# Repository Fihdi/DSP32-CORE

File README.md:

# DSP32-Core

DSP32-Core is a small (4cm x 2cm) audio development board based on the ESP32-S3. This board can be used as the core for digital music and audio applications involving synthesizers, samplers, digital effects, sequencers, etc. The SPI interface allows to connect an SD-card to the board and save and replay music and project settings.

# Features
+ Stereo audio in- and output
+ 3.3V and 5V voltage regulator
+ USB and SPI Interface
+ up to 15 GPIO pins
+ PCM1808 ADC
+ PCM5102 DAC.
# Pinout

PCB fabrication sponsored by [PCBWay](https://pcbway.com). Their excellent PCB assembly service allows the DSP32-CORE to be produced in with every component perfectly soldered. Simply upload the production files like gerbers, position and BOM files and receive your fully assembled audio development board. High PCB quality and good customer service throughout the process makes PCBWay a reliable partner.

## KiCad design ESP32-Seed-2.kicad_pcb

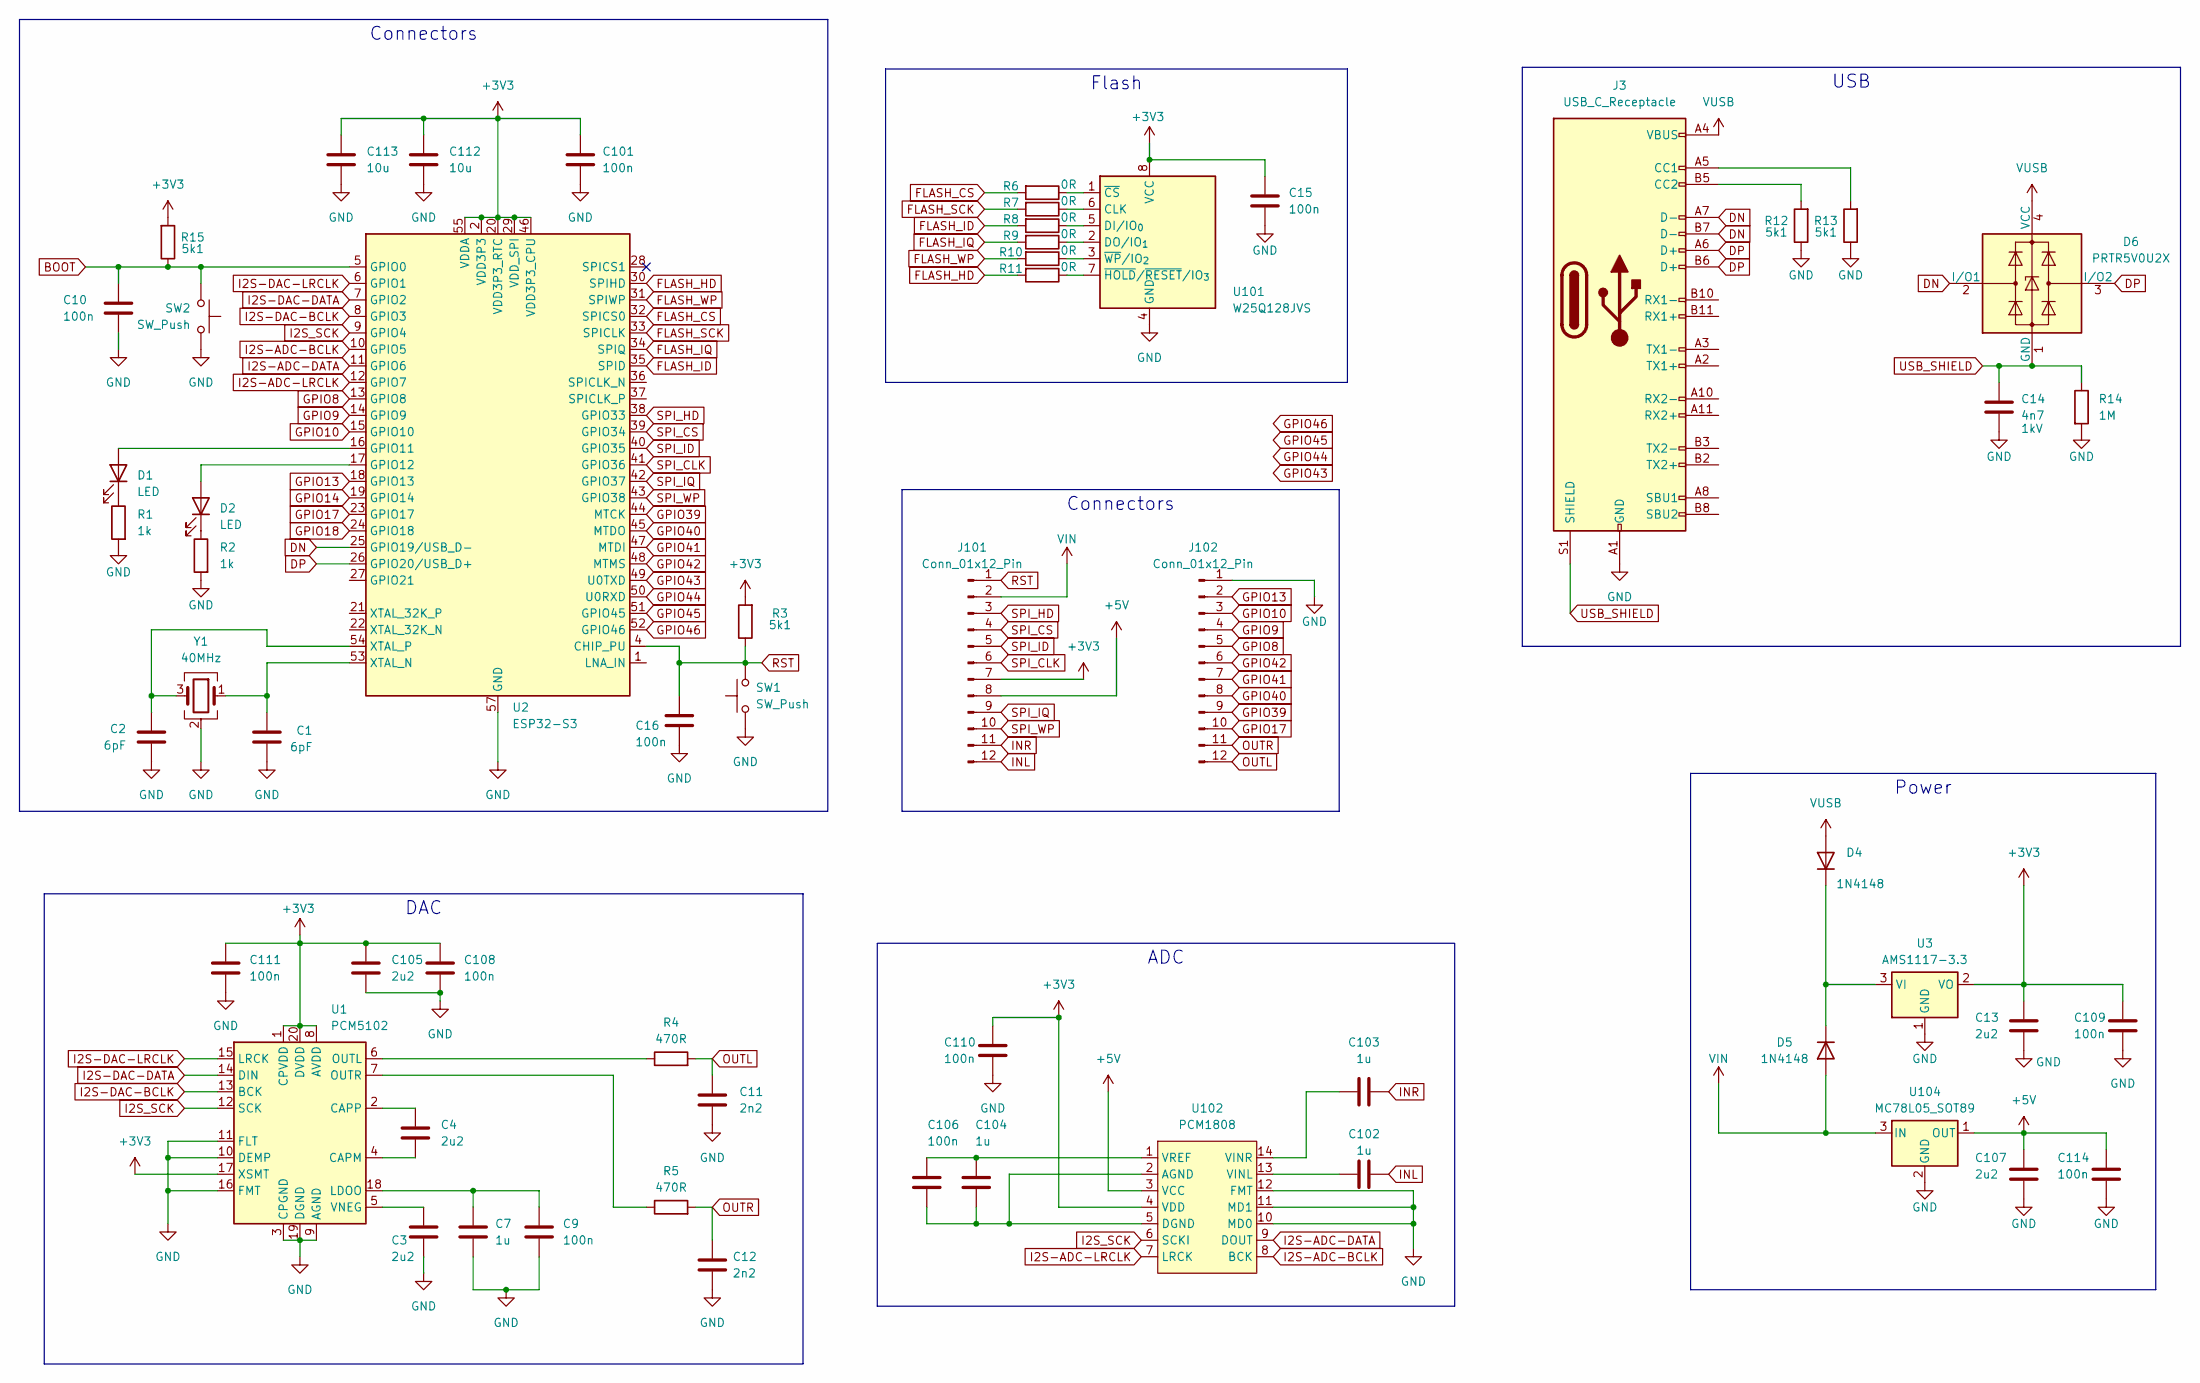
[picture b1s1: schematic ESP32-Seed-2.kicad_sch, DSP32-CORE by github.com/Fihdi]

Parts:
C1, C2: 6pF; C_0603_1608Metric
C3, C4, C13, C105, C107: 2u2; C_0603_1608Metric
C7, C102, C103, C104: 1u; C_0603_1608Metric
C9, C10, C15, C16, C101, C106, C108, C109, C110, C111, C114: 100n; C_0603_1608Metric
C11, C12: 2n2; C_0603_1608Metric
C14: 4n7; C_0603_1608Metric
C112, C113: 10u; C_0603_1608Metric
D1, D2: LED; LED_0603_1608Metric
D4, D5: 1N4148; D_SOD-323_HandSoldering
D6: PRTR5V0U2X; SOT-143
J3: USB_C_Receptacle; USB_C_Receptacle_GCT_USB4105-xx-A_16P_TopMnt_Horizontal
J101, J102: Conn_01x12_Pin; PinHeader_1x12_P2.54mm_Vertical
R1, R2: 1k; R_0603_1608Metric
R3, R12, R13, R15: 5k1; R_0603_1608Metric
R4, R5: 470R; R_0603_1608Metric
R6, R7, R8, R9, R10, R11: 0R; R_0603_1608Metric
R14: 1M; R_0603_1608Metric
SW1, SW2: SW_Push; SW_SPST_PTS810
U1: PCM5102; TSSOP-20_4.4x6.5mm_P0.65mm
U2: ESP32-S3; QFN-56-1EP_7x7mm_P0.4mm_EP4x4mm
U3: AMS1117-3.3; SOT-89-3
U101: W25Q128JVS; SOIC-8_5.3x5.3mm_P1.27mm
U102: PCM1808; TSSOP-14_4.4x5mm_P0.65mm
U104: MC78L05_SOT89; SOT-89-3
Y1: 40MHz; Crystal_SMD_3225-4Pin_3.2x2.5mm

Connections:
+3V3: C13.1, C15.1, C101.1, C105.1, C108.1, C109.1, C110.1, C111.1, C112.1, C113.1, J101.7, R3.2, R15.2, U1.1 (CPVDD), U1.8 (AVDD), U1.17 (XSMT), U1.20 (DVDD), U2.2 (VDD3P3), U2.3 (VDD3P3), U2.20 (VDD3P3_RTC), U2.29 (VDD_SPI), U2.46 (VDD3P3_CPU), U2.55 (VDDA), U2.56 (VDDA), U3.2 (VO), U101.8 (VCC), U102.4 (VDD)
+5V: C107.1, C114.1, J101.8, U102.3 (VCC), U104.1 (OUT)
BOOT: C10.1, R15.1, SW2.2, U2.5 (GPIO0)
DN: D6.2 (I/O1), J3.A7 (D-), J3.B7 (D-), U2.25 (GPIO19/USB_D-)
DP: D6.3 (I/O2), J3.A6 (D+), J3.B6 (D+), U2.26 (GPIO20/USB_D+)
FLASH_CS: R6.2, U2.32 (SPICS0)
FLASH_HD: R11.2, U2.30 (SPIHD)
FLASH_ID: R8.2, U2.35 (SPID)
FLASH_IQ: R9.2, U2.34 (SPIQ)
FLASH_SCK: R7.2, U2.33 (SPICLK)
FLASH_WP: R10.2, U2.31 (SPIWP)
GND: C1.2, C2.2, C3.2, C7.2, C9.2, C10.2, C11.2, C12.2, C13.2, C14.2, C15.2, C16.2, C101.2, C105.2, C107.2, C108.2, C109.2, C110.2, C111.2, C112.2, C113.2, C114.2, J3.A1 (GND), J3.A12 (GND), J3.B1 (GND), J3.B12 (GND), J102.1, R1.2, R2.2, R12.1, R13.1, R14.2, SW1.1, SW2.1, U1.3 (CPGND), U1.9 (AGND), U1.10 (DEMP), U1.11 (FLT), U1.16 (FMT), U1.19 (DGND), U2.57 (GND), U3.1 (GND), U101.4 (GND), U102.10 (MD0), U102.11 (MD1), U102.12 (FMT), U104.2 (GND), Y1.2 (G), Y1.4 (G)
GPIO8: J102.5, U2.13 (GPIO8)
GPIO9: J102.4, U2.14 (GPIO9)
GPIO10: J102.3, U2.15 (GPIO10)
GPIO13: J102.2, U2.18 (GPIO13)
GPIO14: U2.19 (GPIO14)
GPIO17: J102.10, U2.23 (GPIO17)
GPIO18: U2.24 (GPIO18)
GPIO39: J102.9, U2.44 (MTCK)
GPIO40: J102.8, U2.45 (MTDO)
GPIO41: J102.7, U2.47 (MTDI)
GPIO42: J102.6, U2.48 (MTMS)
GPIO43: U2.49 (U0TXD)
GPIO44: U2.50 (U0RXD)
GPIO45: U2.51 (GPIO45)
GPIO46: U2.52 (GPIO46)
I2S-ADC-BCLK: U2.10 (GPIO5), U102.8 (BCK)
I2S-ADC-DATA: U2.11 (GPIO6), U102.9 (DOUT)
I2S-ADC-LRCLK: U2.12 (GPIO7), U102.7 (LRCK)
I2S-DAC-BCLK: U1.13 (BCK), U2.8 (GPIO3)
I2S-DAC-DATA: U1.14 (DIN), U2.7 (GPIO2)
I2S-DAC-LRCLK: U1.15 (LRCK), U2.6 (GPIO1)
I2S_SCK: U1.12 (SCK), U2.9 (GPIO4), U102.6 (SCKI)
INL: C102.2, J101.12
INR: C103.2, J101.11
unnamed: D1.2 (A), U2.16 (GPIO11)
unnamed: D1.1 (K), R1.1
unnamed: D2.2 (A), U2.17 (GPIO12)
unnamed: D2.1 (K), R2.1
unnamed: D4.1 (K), D5.1 (K), U3.3 (VI)
unnamed: J3.A5 (CC1), R13.2
unnamed: J3.B5 (CC2), R12.2
unnamed: C4.2, U1.4 (CAPM)
unnamed: C4.1, U1.2 (CAPP)
unnamed: C7.1, C9.1, U1.18 (LDOO)
unnamed: R4.1, U1.6 (OUTL)
unnamed: R5.1, U1.7 (OUTR)
unnamed: C3.1, U1.5 (VNEG)
unnamed: C1.1, U2.53 (XTAL_N), Y1.1
unnamed: C2.1, U2.54 (XTAL_P), Y1.3
unnamed: R7.1, U101.6 (CLK)
unnamed: R8.1, U101.5 (DI/IO_{0})
unnamed: R9.1, U101.2 (DO/IO_{1})
unnamed: R6.1, U101.1 (~CS)
unnamed: R11.1, U101.7 (~HOLD/~RESET/IO_{3})
unnamed: R10.1, U101.3 (~WP/IO_{2})
unnamed: C104.2, C106.2, U102.2 (AGND), U102.5 (DGND)
unnamed: C102.1, U102.13 (VINL)
unnamed: C103.1, U102.14 (VINR)
unnamed: C104.1, C106.1, U102.1 (VREF)
OUTL: C11.1, J102.12, R4.2
OUTR: C12.1, J102.11, R5.2
RST: C16.1, J101.1, R3.1, SW1.2, U2.4 (CHIP_PU)
SPI_CLK: J101.6, U2.41 (GPIO36)
SPI_CS: J101.4, U2.39 (GPIO34)
SPI_HD: J101.3, U2.38 (GPIO33)
SPI_ID: J101.5, U2.40 (GPIO35)
SPI_IQ: J101.9, U2.42 (GPIO37)
SPI_WP: J101.10, U2.43 (GPIO38)
USB_SHIELD: C14.1, D6.1 (GND), J3.S1 (SHIELD), R14.1
VIN: D5.2 (A), J101.2, U104.3 (IN)
VUSB: D4.2 (A), D6.4 (VCC), J3.A4 (VBUS), J3.A9 (VBUS), J3.B4 (VBUS), J3.B9 (VBUS)

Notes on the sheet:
DAC
Connectors
Power
ADC
Flash
USB

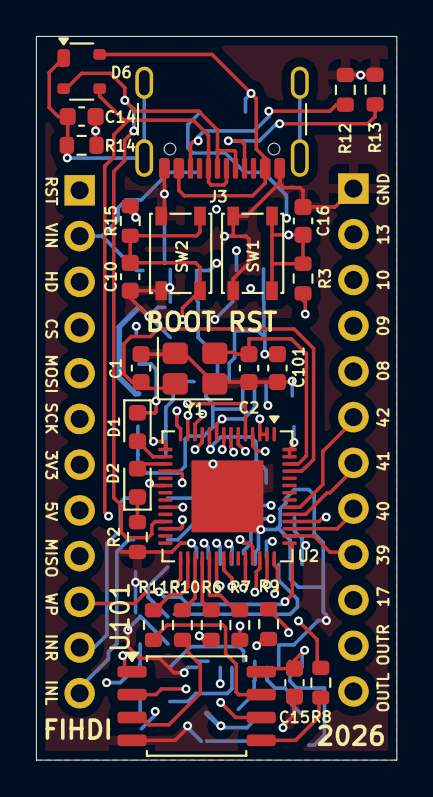
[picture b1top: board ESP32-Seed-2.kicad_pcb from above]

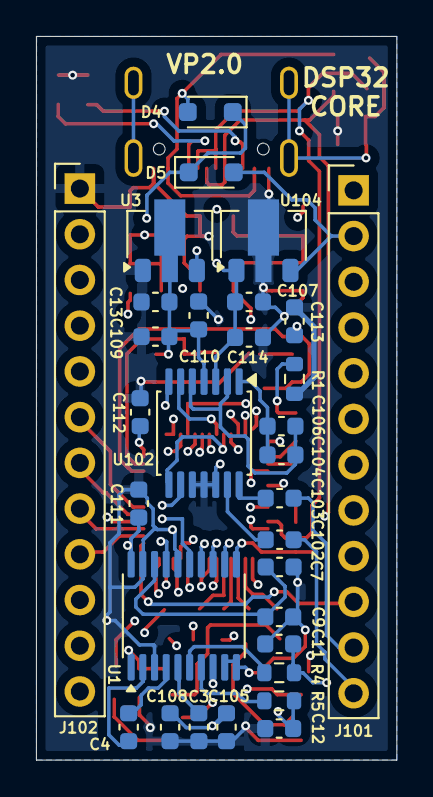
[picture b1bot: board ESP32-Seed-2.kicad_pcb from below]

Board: 4 copper layers, 20.0 x 40.2 mm, 59 parts (31 on the bottom side), 67 nets.

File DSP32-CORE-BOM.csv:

"Reference","Qty","Value","DNP","Exclude from BOM","Exclude from Board","Footprint","Datasheet"
"C1,C2","2","6pF","","","","Capacitor_SMD:C_0603_1608Metric","~"
"C3,C4,C13,C105,C107","5","2u2","","","","Capacitor_SMD:C_0603_1608Metric","~"
"C7,C102,C103,C104","4","1u","","","","Capacitor_SMD:C_0603_1608Metric","~"
"C9,C10,C15,C16,C101,C106,C108,C109,C110,C111,C114","11","100n","","","","Capacitor_SMD:C_0603_1608Metric","~"
"C11,C12","2","2n2","","","","Capacitor_SMD:C_0603_1608Metric","~"
"C14","1","4n7","","","","Capacitor_SMD:C_0603_1608Metric","~"
"C112,C113","2","10u","","","","Capacitor_SMD:C_0603_1608Metric","~"
"D1,D2","2","LED","","","","LED_SMD:LED_0603_1608Metric","~"
"D4,D5","2","1N4148","","","","Diode_SMD:D_SOD-323_HandSoldering","~"
"D6","1","PRTR5V0U2X","","","","Package_TO_SOT_SMD:SOT-143","https://assets.nexperia.com/documents/data-sheet/PRTR5V0U2X.pdf"
"J3","1","USB_C_Receptacle","","","","Connector_USB:USB_C_Receptacle_GCT_USB4105-xx-A_16P_TopMnt_Horizontal","https://www.usb.org/sites/default/files/documents/usb_type-c.zip"
"J101,J102","2","Conn_01x12_Pin","","","","Connector_PinHeader_2.54mm:PinHeader_1x12_P2.54mm_Vertical","~"
"R1,R2","2","1k","","","","Resistor_SMD:R_0603_1608Metric","~"
"R3,R12,R13,R15","4","5k1","","","","Resistor_SMD:R_0603_1608Metric","~"
"R4,R5","2","470R","","","","Resistor_SMD:R_0603_1608Metric","~"
"R6,R7,R8,R9,R10,R11","6","0R","","","","Resistor_SMD:R_0603_1608Metric","~"
"R14","1","1M","","","","Resistor_SMD:R_0603_1608Metric","~"
"SW1,SW2","2","SW_Push","","","","Button_Switch_SMD:SW_SPST_PTS810","~"
"U1","1","PCM5102","","","","Package_SO:TSSOP-20_4.4x6.5mm_P0.65mm","http://www.ti.com/lit/ds/symlink/pcm5102.pdf"
"U2","1","ESP32-S3","","","","Package_DFN_QFN:QFN-56-1EP_7x7mm_P0.4mm_EP4x4mm","https://www.espressif.com/sites/default/files/documentation/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"
"U3","1","AMS1117-3.3","","","","Package_TO_SOT_SMD:SOT-89-3","http://www.advanced-monolithic.com/pdf/ds1117.pdf"
"U101","1","W25Q128JVS","","","","Package_SO:SOIC-8_5.3x5.3mm_P1.27mm","https://www.winbond.com/resource-files/w25q128jv_dtr%20revc%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"
"U102","1","PCM1808","","","","Package_SO:TSSOP-14_4.4x5mm_P0.65mm",""
"U104","1","MC78L05_SOT89","","","","Package_TO_SOT_SMD:SOT-89-3","https://www.onsemi.com/pub/Collateral/MC78L00A-D.PDF"
"Y1","1","40MHz","","","","Crystal:Crystal_SMD_3225-4Pin_3.2x2.5mm","~"
